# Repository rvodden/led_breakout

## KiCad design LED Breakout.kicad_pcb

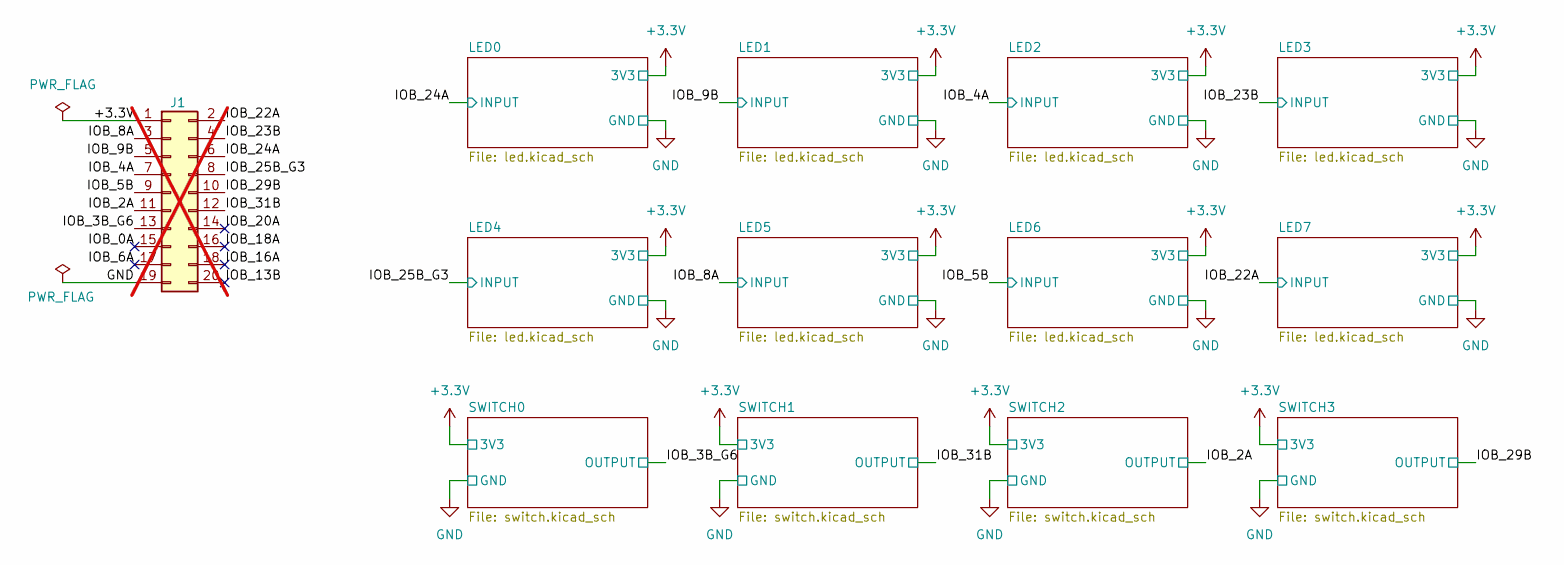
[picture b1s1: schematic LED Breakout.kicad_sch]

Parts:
J1: Conn_02x10_Odd_Even; PinHeader_2x10_P2.54mm_Vertical; not fitted

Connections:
+3.3V: J1.1; also elsewhere on the board
/IOB_0A: J1.15
/IOB_2A: J1.11; also elsewhere on the board
/IOB_3B_G6: J1.13; also elsewhere on the board
/IOB_4A: J1.7; also elsewhere on the board
/IOB_5B: J1.9; also elsewhere on the board
/IOB_6A: J1.17
/IOB_8A: J1.3; also elsewhere on the board
/IOB_9B: J1.5; also elsewhere on the board
/IOB_13B: J1.20
/IOB_16A: J1.18
/IOB_18A: J1.16
/IOB_20A: J1.14
/IOB_22A: J1.2; also elsewhere on the board
/IOB_23B: J1.4; also elsewhere on the board
/IOB_24A: J1.6; also elsewhere on the board
/IOB_25B_G3: J1.8; also elsewhere on the board
/IOB_29B: J1.10; also elsewhere on the board
/IOB_31B: J1.12; also elsewhere on the board
GND: J1.19; also elsewhere on the board

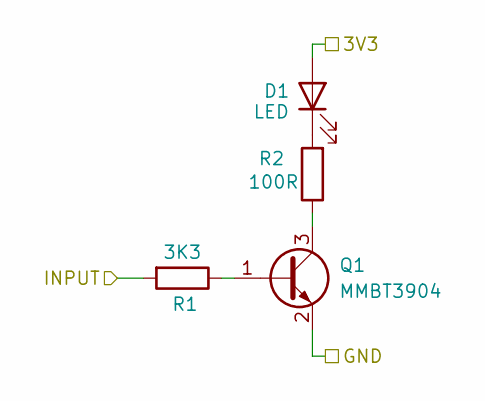
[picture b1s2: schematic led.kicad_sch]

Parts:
D1: LED; LED_0603_1608Metric; LCSC C2286
Q1: MMBT3904; SOT-23; LCSC C7420353
R1: 3K3; R_0402_1005Metric; LCSC C25890
R2: 100R; R_0402_1005Metric; LCSC C25076

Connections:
+3.3V: D1.2 (A); also elsewhere on the board
/IOB_24A: R1.2; also elsewhere on the board
GND: Q1.2 (E); also elsewhere on the board
unnamed: D1.1 (K), R2.2
unnamed: Q1.1 (B), R1.1
unnamed: Q1.3 (C), R2.1

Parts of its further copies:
D2, D3, D4, D5, D6, D7, D8: LED; LED_0603_1608Metric; LCSC C2286
Q2, Q3, Q4, Q5, Q6, Q7, Q8: MMBT3904; SOT-23; LCSC C7420353
R3, R5, R7, R9, R11, R13, R15: 3K3; R_0402_1005Metric; LCSC C25890
R4, R6, R8, R10, R12, R14, R16: 100R; R_0402_1005Metric; LCSC C25076

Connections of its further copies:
+3.3V: D2.2 (A), D3.2 (A), D4.2 (A), D5.2 (A), D6.2 (A), D7.2 (A), D8.2 (A); also elsewhere on the board
/IOB_4A: R5.2; also elsewhere on the board
/IOB_5B: R13.2; also elsewhere on the board
/IOB_8A: R11.2; also elsewhere on the board
/IOB_9B: R3.2; also elsewhere on the board
/IOB_22A: R15.2; also elsewhere on the board
/IOB_23B: R7.2; also elsewhere on the board
/IOB_25B_G3: R9.2; also elsewhere on the board
GND: Q2.2 (E), Q3.2 (E), Q4.2 (E), Q5.2 (E), Q6.2 (E), Q7.2 (E), Q8.2 (E); also elsewhere on the board
unnamed: D2.1 (K), R4.2
unnamed: D3.1 (K), R6.2
unnamed: D4.1 (K), R8.2
unnamed: D5.1 (K), R10.2
unnamed: D6.1 (K), R12.2
unnamed: D7.1 (K), R14.2
unnamed: D8.1 (K), R16.2
unnamed: Q2.1 (B), R3.1
unnamed: Q2.3 (C), R4.1
unnamed: Q3.1 (B), R5.1
unnamed: Q3.3 (C), R6.1
unnamed: Q4.1 (B), R7.1
unnamed: Q4.3 (C), R8.1
unnamed: Q5.1 (B), R9.1
unnamed: Q5.3 (C), R10.1
unnamed: Q6.1 (B), R11.1
unnamed: Q6.3 (C), R12.1
unnamed: Q7.1 (B), R13.1
unnamed: Q7.3 (C), R14.1
unnamed: Q8.1 (B), R15.1
unnamed: Q8.3 (C), R16.1

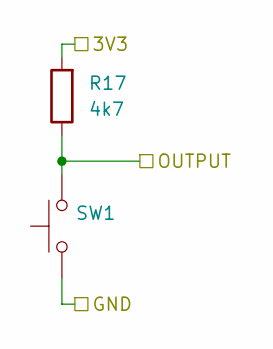
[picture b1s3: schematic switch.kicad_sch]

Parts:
R17: 4k7; R_0402_1005Metric; LCSC C25900
SW1: KMR231NG; SW_Push_1P1T_NO_CK_KMR2; LCSC C221680

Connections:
+3.3V: R17.2; also elsewhere on the board
/IOB_3B_G6: R17.1, SW1.2; also elsewhere on the board
GND: SW1.1; also elsewhere on the board

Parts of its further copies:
R18, R19, R20: 4k7; R_0402_1005Metric; LCSC C25900
SW2, SW3, SW4: KMR231NG; SW_Push_1P1T_NO_CK_KMR2; LCSC C221680

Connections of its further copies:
+3.3V: R18.2, R19.2, R20.2; also elsewhere on the board
/IOB_2A: R19.1, SW3.2; also elsewhere on the board
/IOB_29B: R20.1, SW4.2; also elsewhere on the board
/IOB_31B: R18.1, SW2.2; also elsewhere on the board
GND: SW2.1, SW3.1, SW4.1; also elsewhere on the board

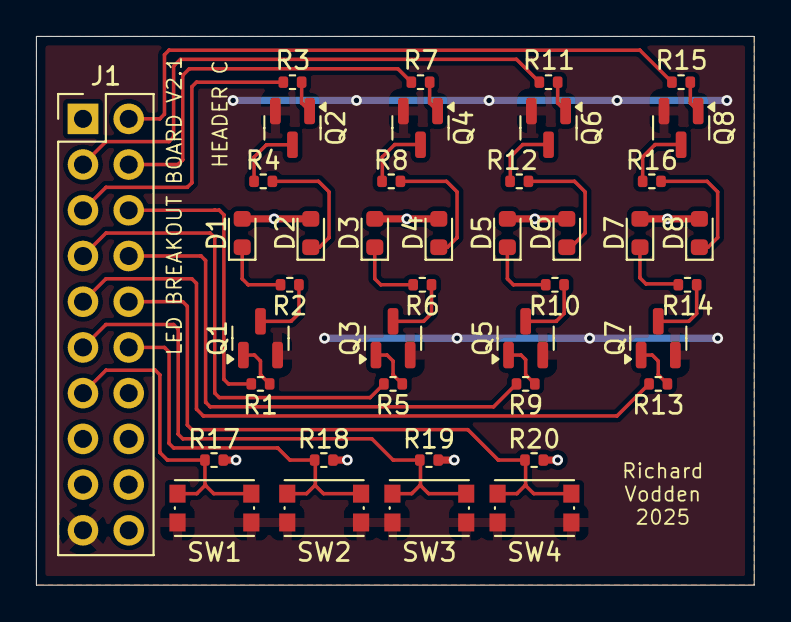
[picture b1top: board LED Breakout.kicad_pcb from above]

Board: 2 copper layers, 39.9 x 30.5 mm, 41 parts (0 on the bottom side), 38 nets.

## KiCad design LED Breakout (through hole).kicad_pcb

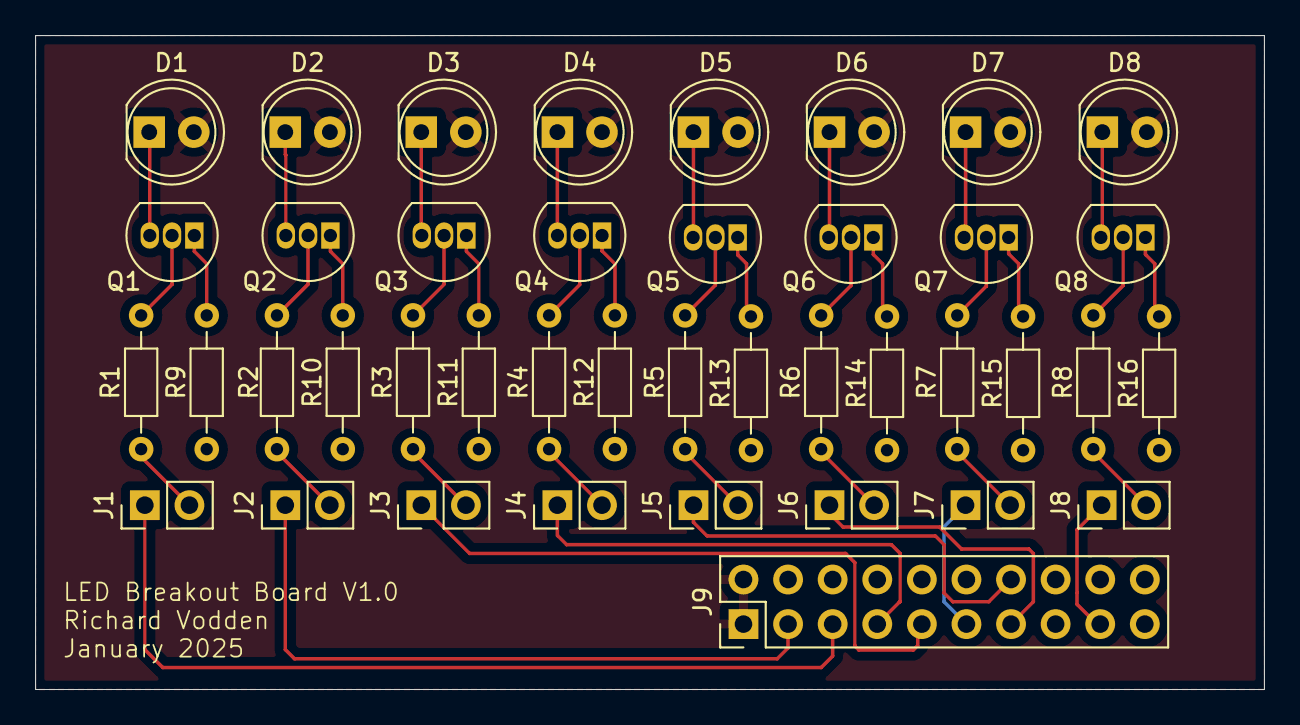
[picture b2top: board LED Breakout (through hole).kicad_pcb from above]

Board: 2 copper layers, 70.0 x 37.2 mm, 41 parts (0 on the bottom side), 42 nets.

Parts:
D1, D2, D3, D4, D5, D6, D7, D8: LED; LED_D5.0mm
J1, J2, J3, J4, J5, J6, J7, J8: Conn_01x02_Pin; PinHeader_1x02_P2.54mm_Vertical
J9: Conn_02x10_Odd_Even; PinHeader_2x10_P2.54mm_Vertical
Q1, Q2, Q3, Q4, Q5, Q6, Q7, Q8: 2N3904; TO-92_Inline
R1, R2, R3, R4, R5, R6, R7, R8, R9, R10, R11, R12, R13, R14, R15, R16: R; R_Axial_DIN0204_L3.6mm_D1.6mm_P7.62mm_Horizontal

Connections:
+3.3V: D1.2 (A), D2.2 (A), D3.2 (A), D4.2 (A), D5.2 (A), D6.2 (A), D7.2 (A), D8.2 (A), J9.1, J9.2
/IOT_36B: J1.1, J9.5
/IOT_37A: J2.1, J9.3
/IOT_38B: J3.1, J9.9
/IOT_39A: J4.1, J9.7
/IOT_41A: J5.1, J9.14
/IOT_42B: J6.1, J9.13
/IOT_43A: J7.1, J9.11
/IOT_44B: J8.1, J9.17
GND: J9.18, J9.20, R9.1, R10.1, R11.1, R12.1, R13.1, R14.1, R15.1, R16.1
unnamed: D1.1 (K), Q1.3 (C)
unnamed: D2.1 (K), Q2.3 (C)
unnamed: D3.1 (K), Q3.3 (C)
unnamed: D4.1 (K), Q4.3 (C)
unnamed: D5.1 (K), Q5.3 (C)
unnamed: D6.1 (K), Q6.3 (C)
unnamed: D7.1 (K), Q7.3 (C)
unnamed: D8.1 (K), Q8.3 (C)
unnamed: J1.2, R1.1
unnamed: J2.2, R2.1
unnamed: J3.2, R3.1
unnamed: J4.2, R4.1
unnamed: J5.2, R5.1
unnamed: J6.2, R6.1
unnamed: J7.2, R7.1
unnamed: J8.2, R8.1
unnamed: Q1.2 (B), R1.2
unnamed: Q1.1 (E), R9.2
unnamed: Q2.2 (B), R2.2
unnamed: Q2.1 (E), R10.2
unnamed: Q3.2 (B), R3.2
unnamed: Q3.1 (E), R11.2
unnamed: Q4.2 (B), R4.2
unnamed: Q4.1 (E), R12.2
unnamed: Q5.2 (B), R5.2
unnamed: Q5.1 (E), R13.2
unnamed: Q6.2 (B), R6.2
unnamed: Q6.1 (E), R14.2
unnamed: Q7.2 (B), R7.2
unnamed: Q7.1 (E), R15.2
unnamed: Q8.2 (B), R8.2
unnamed: Q8.1 (E), R16.2

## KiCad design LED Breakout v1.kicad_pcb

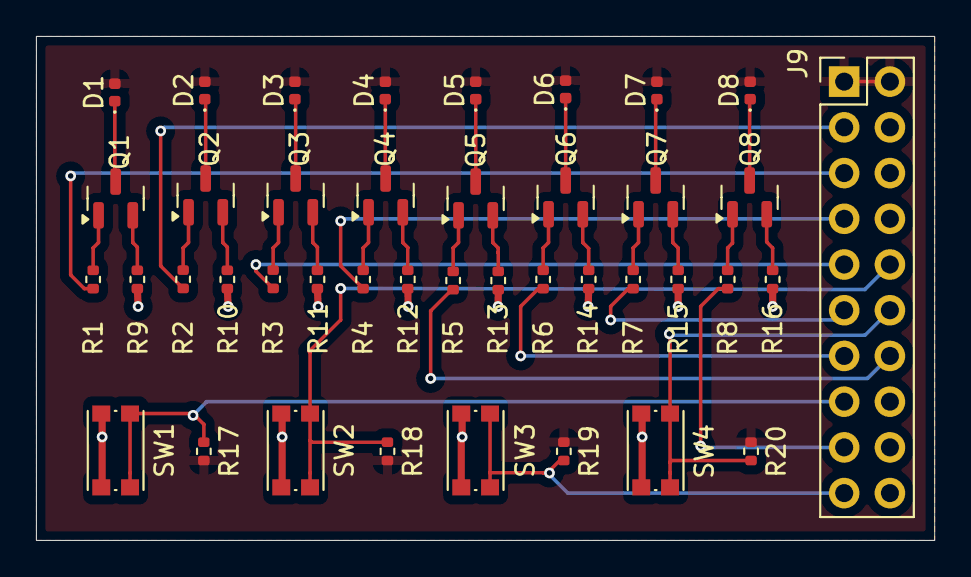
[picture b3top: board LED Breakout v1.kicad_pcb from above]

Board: 2 copper layers, 49.9 x 28.0 mm, 41 parts (0 on the bottom side), 38 nets.

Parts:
D1, D2, D3, D4, D5, D6, D7, D8: LED; LED_0402_1005Metric
J9: Conn_02x10_Odd_Even; PinHeader_2x10_P2.54mm_Vertical
Q1, Q2, Q3, Q4, Q5, Q6, Q7, Q8: MMBT3904; SOT-23
R1, R2, R3, R4, R5, R6, R7, R8: 470R; R_0402_1005Metric
R9, R10, R11, R12, R13, R14, R15, R16: 68R; R_0402_1005Metric
R17, R18, R19, R20: 4k7; R_0402_1005Metric
SW1, SW2, SW3, SW4: NANOT 160 AS; SW_Push_1P1T_NO_CK_KMR2

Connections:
+3.3V: D1.2 (A), D2.2 (A), D3.2 (A), D4.2 (A), D5.2 (A), D6.2 (A), D7.2 (A), D8.2 (A), J9.1, J9.2, R17.2, R18.2, R19.2, R20.2
/IOT_36B: J9.5, R1.1
/IOT_37A: J9.3, R2.1
/IOT_38B: J9.9, R3.1
/IOT_39A: J9.7, R4.1
/IOT_41A: J9.14, R5.1
/IOT_42B: J9.13, R6.1
/IOT_43A: J9.11, R7.1
/IOT_44B: J9.17, R8.1
/IOT_45A: J9.15, R17.1, SW1.2
/IOT_48B: J9.10, R18.1, SW2.2
/IOT_49A: J9.19, R19.1, SW3.2
/IOT_50B: J9.12, R20.1, SW4.2
GND: J9.18, J9.20, R9.1, R10.1, R11.1, R12.1, R13.1, R14.1, R15.1, R16.1, SW1.1, SW2.1, SW3.1, SW4.1
unnamed: D1.1 (K), Q1.3 (C)
unnamed: D2.1 (K), Q2.3 (C)
unnamed: D3.1 (K), Q3.3 (C)
unnamed: D4.1 (K), Q4.3 (C)
unnamed: D5.1 (K), Q5.3 (C)
unnamed: D6.1 (K), Q6.3 (C)
unnamed: D7.1 (K), Q7.3 (C)
unnamed: D8.1 (K), Q8.3 (C)
unnamed: Q1.2 (E), R9.2
unnamed: Q1.1 (B), R1.2
unnamed: Q2.2 (E), R10.2
unnamed: Q2.1 (B), R2.2
unnamed: Q3.2 (E), R11.2
unnamed: Q3.1 (B), R3.2
unnamed: Q4.2 (E), R12.2
unnamed: Q4.1 (B), R4.2
unnamed: Q5.2 (E), R13.2
unnamed: Q5.1 (B), R5.2
unnamed: Q6.2 (E), R14.2
unnamed: Q6.1 (B), R6.2
unnamed: Q7.2 (E), R15.2
unnamed: Q7.1 (B), R7.2
unnamed: Q8.2 (E), R16.2
unnamed: Q8.1 (B), R8.2

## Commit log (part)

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2025-07-13 Added LSCS part numbers to all components
2025-07-15 configure ci
2025-07-15 Label connector pins which have no connections
2025-07-15 Corrected power flags to fix ERC test
2025-07-16 Improved layout to remove symbol warnings
